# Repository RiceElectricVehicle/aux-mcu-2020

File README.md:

# Central Controller Code

Initial Author: Boyuan Deng

## Overview

This library is built for Rice Electric Vehicle Electric Team's auxilary board (aux board). The main function of the auxilary board include the following:

1. Take in and respond to information from pedal and break
2. Communicate with and respond to motor controller
3. Enable lighting control through switches installed on board
4. Display the car's status on screen

All the functions mentioned above requires the microcontroller on aux board. We've chosen Teensy 3.5 as the microcontroller, and the language for it is Arduino language, which is essentially C++ with Arduino's special libraries. We chose Serial Peripheral Interface (SPI) as the protocol between the aux board and the motor controller board. The following sections will detail the libraries and files contained in the library.

## External Libraries

Besides main.cpp, there are two external libraries under the /lib directory. You can add additional directories to /lib. Refer to the README under /lib to find out how to do that.

### Arduino-PID-Library-master

The Proportioal-Integral-Derivative (PID) control is a control loop mechanism used widely in industry. If you are unfamiliar with this, be sure to do some online research to understand it. The basic idea is to read a sensor, then compute the desired actuator output by calculating proportional, integral, and derivative responses and summing those three components to compute the output.

This library is an external libarary provided by Arduino. It is currently unused as the PID functionality has been taken care of by the motor controller. However, it still comes handy if you ever want PID in aux board. The constructor of the class is as below:
```
PID(double* Input, double* Output, double* Setpoint, double Kp, double Ki,
         double Kd, int POn, int ControllerDirection)
```
The PID input will be stored in first pointer, and the output second pointer, the setpoint third pointer. Three constants Kp, Ki and Kd are also required. You can specify the direction by last variable. A typical initialization of a PID object would look like below:
```
double pid_inA, pid_outA, pid_setA;
PID pidA(&pid_inA, &pid_outA, &pid_setA, 1, 1, 0, REVERSE);
```
Then in the main loop, you call
```
pidA.Compute();
```
And then `pid_outA` will contain desired output.

### OLED

This is a library that I personally write to drive the OLED screen. **Please install U8g2 in PlatformIO/your preferred IDE before it will work!** It is dependent on U8g2 libarary. A typical initialization would look like this:
```
OLED OLED_screen;
```
Internally a U8g2 screen object of the required type will be initialized. Then in your setup() routine, initializa the object by passing in a pointer to a location where the speed/power/whatever you want to show is stored:
```
OLED_screen.init(&speed);
```
After that, you can call it's functions like `display_braking`, `display_speed` etc. Some functions inside it is outdated, and you can add or replace some of them if you want.

## Main Code

Under /src directory are main control algorithms for the car.

### pins.h

Here we define necessary pins for main.cpp to use. In this way, we no longer need to memorize the pins for each functionality after we settled the design. You can find a pinout for Teensy 3.5 here:

https://www.pjrc.com/teensy/card8a_rev2.pdf

### main.cpp

This is the main control algorithm for aux board. I will explain some important variables I declared before I move to the algorithm itself.

##### Data

In SPI communication, we are transmitting 16 bits of information in forms of an integer. Manipulating this integer is a little trouble some, and `Data` is more easy to play with. `create_data()`, `decode_data()`, `encode_data()` and `print_data()` are self-explanatory helper functions to aid transition between struct and int.

##### Message ints

```
volatile unsigned int message_A_out;
volatile unsigned int message_A_in = 0;
volatile unsigned int message_B_out;
volatile unsigned int message_B_in = 0;
```
These are the variables we use to receive and send information over SPI. Rules for their encoding is explained in next section.

##### brk, direction and error

These are global variables keeping track of current state of the car.

##### The IntervalTimer objects

```
IntervalTimer clock_timer;
IntervalTimer SPI_timer;
```
These two IntervalTimer objects utilizes Teensy 3.5's hardware timed interrupts. They send out interrupt signals every certain amount of time, so that the designated function will execute every fixed amount of time. Meanwhile, main loop will pause.

#### The setup() routine

Here a few things need to be set up:

1. Set pinMode for necessary pins
2. Serial monitor, enabling debugging
3. Interrupt for break, as well we the IntervalTimer objects
4. SPI communication
5. OLED screen object

Refer to the code comments for implementation details.

#### The loop() routine

Currently useless. Important routines are wrapped inside IntervalTimer objects so they can be steadily and predicably executed every certain amount of time. However, potentially it can be used to monitor motor controller's state and react to it accordingly.

#### The blink() routine

This function send out signals to toggle headlight every half a second, so that it blinks.

#### The brake_isr() routine

Whenever there is a change in the `BRAKE_SNS` pin, this function will be executed. If it is activated when the current state is breaking, that means the brake is released. Otherwise, it means that the brake is been activated, then the current state is changed and we communicate with motor controller this change.

#### The get_and_send() routine

The core routine of main.cpp. First we read in values indicating position of the pedal. We then send this information along with current state over to motor controller. Note that you need to pull the pins low before you transmit the information, and pull the pins high after you finished.

## SPI specification

The information we send over in SPI is an 16-bit integer.

### 4 Most Significant Bits

4MSBs indicat the current state of the car. 1st bit indicate brake, 2nd bit direction, 3rd bit error, 4th bit currently left empty and for future use. For brake and error, 1 indicate "have" while 0 indicate "do not have" (e.g. 1 in brake indicate braking). For direction, 1 is forward while 0 is backward.

### 12 lower bits

12 lower bits are for set points. This allows for a resolution of 1/4096 for set points. The actual representation of the set points are by no means fixed, and feel free to change if you see fit.

### To conclude:

Brake|Direction|Error|Blank|12 bits of set point

#### Exersise:

What does 1100000000001111 mean?

Answer: Braking, forward, no errors and a setpoint of 31.

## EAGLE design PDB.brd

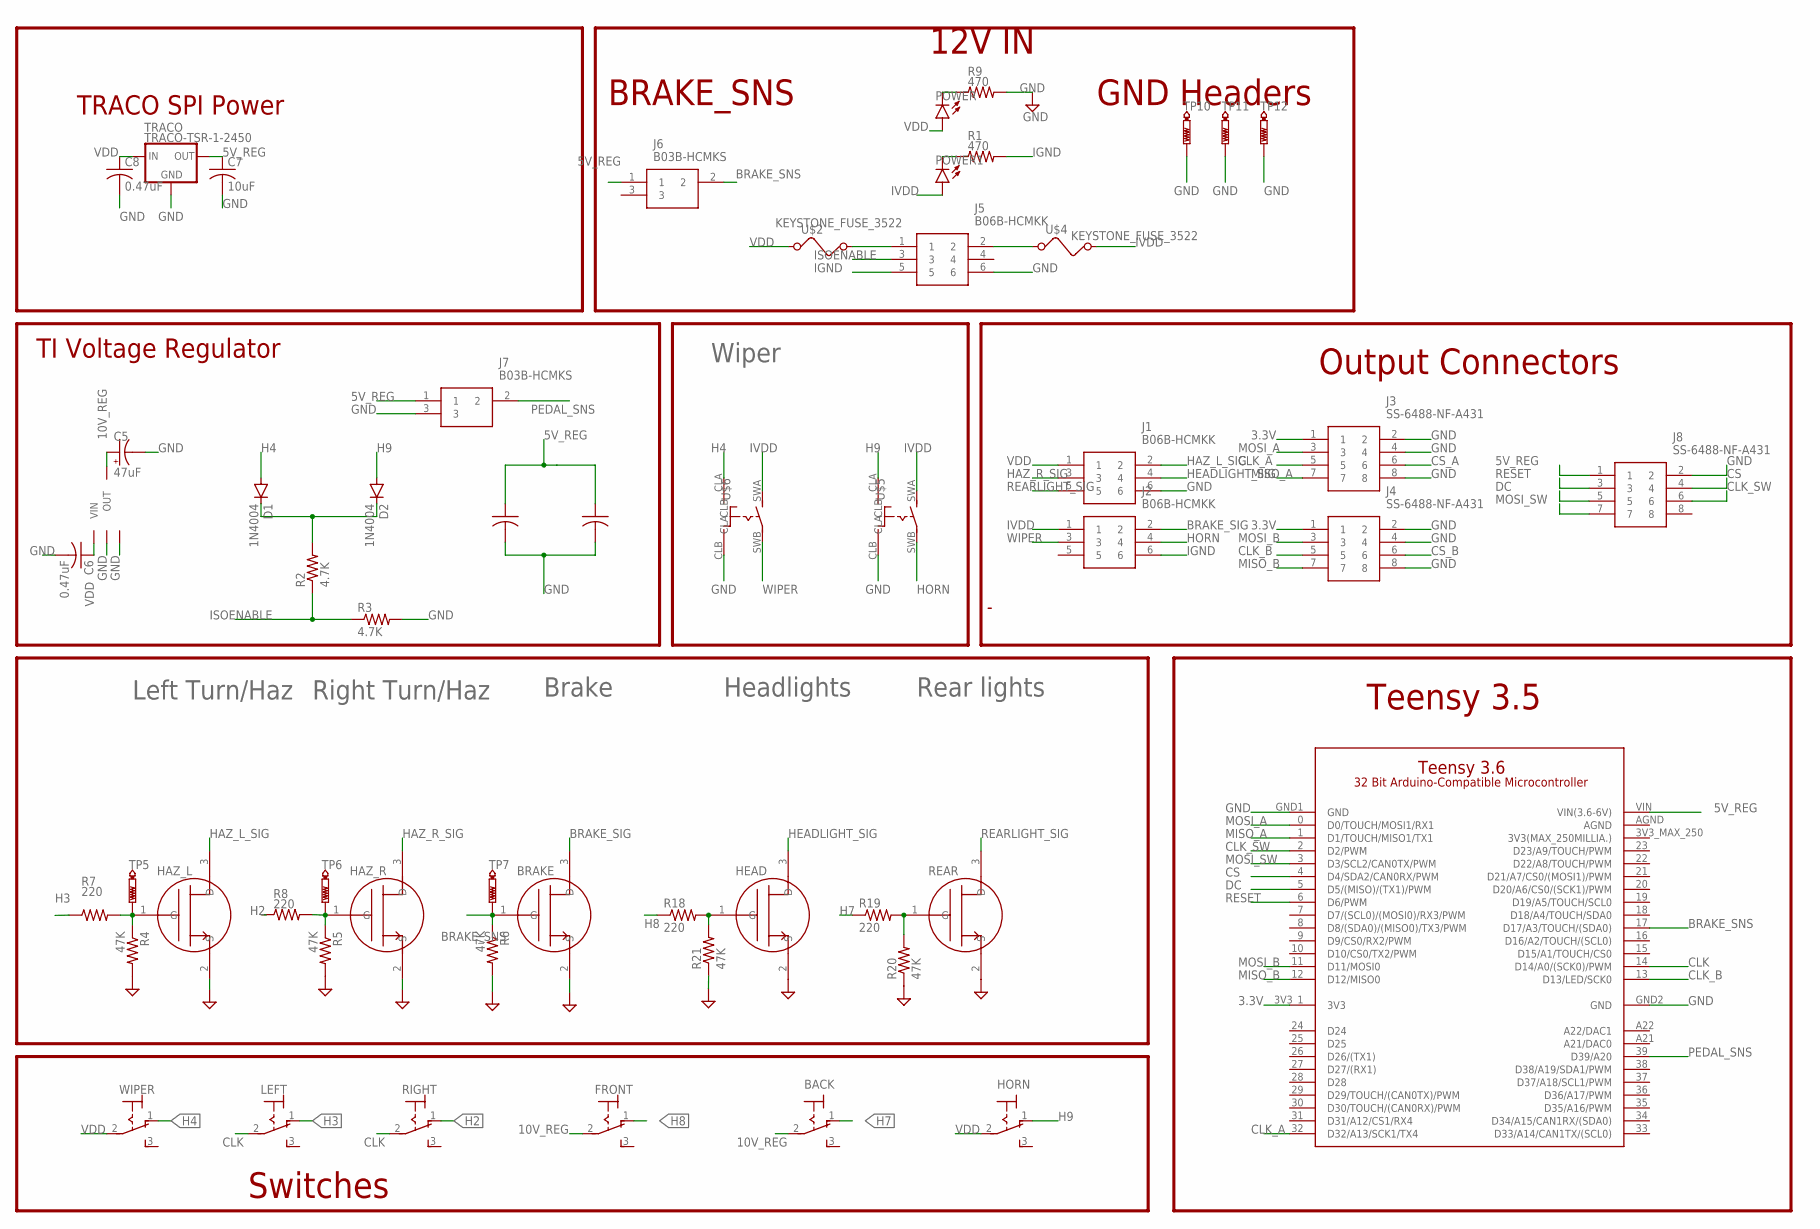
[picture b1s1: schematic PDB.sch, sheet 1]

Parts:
BACK: M9040P
BRAKE: NCV8405ADPAK-3PIN; TO254P1054X240-3
C1: 0.1uF; C0805
C2, C7: 10uF; C0805
C5: 47uF; PANASONIC_C
C6, C8: 0.47uF; C0805
D1, D2: 1N4004; DO41-10
FRONT: M9040P
HAZ_L: NCV8405ADPAK-3PIN; TO254P1054X240-3
HAZ_R: NCV8405ADPAK-3PIN; TO254P1054X240-3
HEAD: NCV8405ADPAK-3PIN; TO254P1054X240-3
HORN: M9040P
J1, J2, J5: B06B-HCMKK; B06BHCMKK
J3, J4, J8: SS-6488-NF-A431; SS6488NFA431
J6, J7: B03B-HCMKS; B03BHCMKS
LEFT: M9040P
LM2940: LM2940LM; SOT230P700X180-4
POWER, POWER1: LEDCHIPLED_0805; CHIPLED_0805
R1, R9: 470; R3225
R2, R3: 4.7K; R0805
R4, R5, R6, R20, R21: 47K; R0805
R7, R8, R18, R19: 220; R0805
REAR: NCV8405ADPAK-3PIN; TO254P1054X240-3
RIGHT: M9040P
TP5, TP6, TP7: PTR1B2,54; B2,54
TP10, TP11, TP12: PTR1PAD1-13Y; P1-13Y
TRACO: TRACO-TSR-1-2450; SIP3
U$2, U$4: KEYSTONE_FUSE_3522
U$3: TEENSY-3.6_ONLY_HOLES
U$5, U$6: TE_CON_OJE-SH-112DM,095\; TE_CON_OJE-SH-112DM,095
WIPER: M9040P

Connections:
3.3V: J3.1, J4.1, U$3.3V3_1 (3V3)
5V_REG: C1.1, C2.1, C7.1, J6.1, J7.1, J8.1, TRACO.3 (OUT), U$3.VIN (VIN(3.6-6V))
10V_REG: BACK.2, C5.+, FRONT.2, LM2940.3 (OUT)
AGND: U$3.AGND
BRAKE_SIG: BRAKE.3 (D), J2.2
BRAKE_SNS: BRAKE.1 (G), J6.2, R6.1, TP7.TP, U$3.17 (D17/A3/TOUCH/(SDA0))
CLK: LEFT.2, RIGHT.2, U$3.14 (D14/A0/(SCK0)/PWM)
CLK_A: J3.5, U$3.32 (D32/A13/SCK1/TX4)
CLK_B: J4.5, U$3.13 (D13/LED/SCK0)
CLK_SW: J8.6, U$3.2 (D2/PWM)
CS: J8.4, U$3.4 (D4/SDA2/CAN0RX/PWM)
CS_A: J3.6
CS_B: J4.6
DC: J8.5, U$3.5 (D5/(MISO)/(TX1)/PWM)
GND: BRAKE.2 (S), C1.2, C2.2, C5.-, C6.2, C7.2, C8.2, HAZ_L.2 (S), HAZ_R.2 (S), HEAD.2 (S), J1.6, J3.2, J3.4, J3.8, J4.2, J4.4, J4.8, J5.6, J7.3, J8.2, LM2940.2 (GND2), LM2940.4 (GND), R3.2, R4.2, R5.2, R6.2, R9.2, R20.1, R21.1, REAR.2 (S), TP10.TP, TP11.TP, TP12.TP, TRACO.2 (GND), U$3.GND1 (GND), U$3.GND2 (GND), U$5.CLB, U$6.CLB
H2: R8.1, RIGHT.1 (O)
H3: LEFT.1 (O), R7.1
H4: D1.A, U$6.CLA, WIPER.1 (O)
H7: BACK.1 (O), R19.1
H8: FRONT.1 (O), R18.1
H9: D2.A, HORN.1 (O), U$5.CLA
HAZ_L_SIG: HAZ_L.3 (D), J1.2
HAZ_R_SIG: HAZ_R.3 (D), J1.3
HEADLIGHT_SIG: HEAD.3 (D), J1.4
HL_GATE: HAZ_L.1 (G), R4.1, R7.2, TP5.TP
HORN: J2.4, U$5.SWB
HR_GATE: HAZ_R.1 (G), R5.1, R8.2, TP6.TP
IGND: J2.6, J5.5, R1.2
ISOENABLE: J5.3, R2.1, R3.1
IVDD: J2.1, POWER1.A, U$4.B1 (2), U$4.B2 (2), U$5.SWA, U$6.SWA
MISO_A: J3.7, U$3.1 (D1/TOUCH/MISO1/TX1)
MISO_B: J4.7, U$3.12 (D12/MISO0)
MOSI_A: J3.3, U$3.0 (D0/TOUCH/MOSI1/RX1)
MOSI_B: J4.3, U$3.11 (D11/MOSI0)
MOSI_SW: J8.7, U$3.3 (D3/SCL2/CAN0TX/PWM)
unnamed: POWER.C, R9.1
unnamed: D1.C, D2.C, R2.2
unnamed: J5.1, U$2.B1 (2), U$2.B2 (2)
unnamed: J5.2, U$4.A1 (1), U$4.A2 (1)
unnamed: POWER1.C, R1.1
unnamed: HEAD.1 (G), R18.2, R21.2
unnamed: R19.2, R20.2, REAR.1 (G)
PEDAL_SNS: J7.2, U$3.39 (D39/A20)
REARLIGHT_SIG: J1.5, REAR.3 (D)
RESET: J8.3, U$3.6 (D6/PWM)
VDD: C6.1, C8.1, HORN.2, J1.1, LM2940.1 (VIN), POWER.A, TRACO.1 (IN), U$2.A1 (1), U$2.A2 (1), WIPER.2
WIPER: J2.3, U$6.SWB

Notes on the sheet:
12V IN
BRAKE_SNS
Switches
Wiper
Left Turn/Haz
Right Turn/Haz
Brake
Headlights
Rear lights
GND Headers
Output Connectors
TRACO SPI Power
TI Voltage Regulator
Teensy 3.5

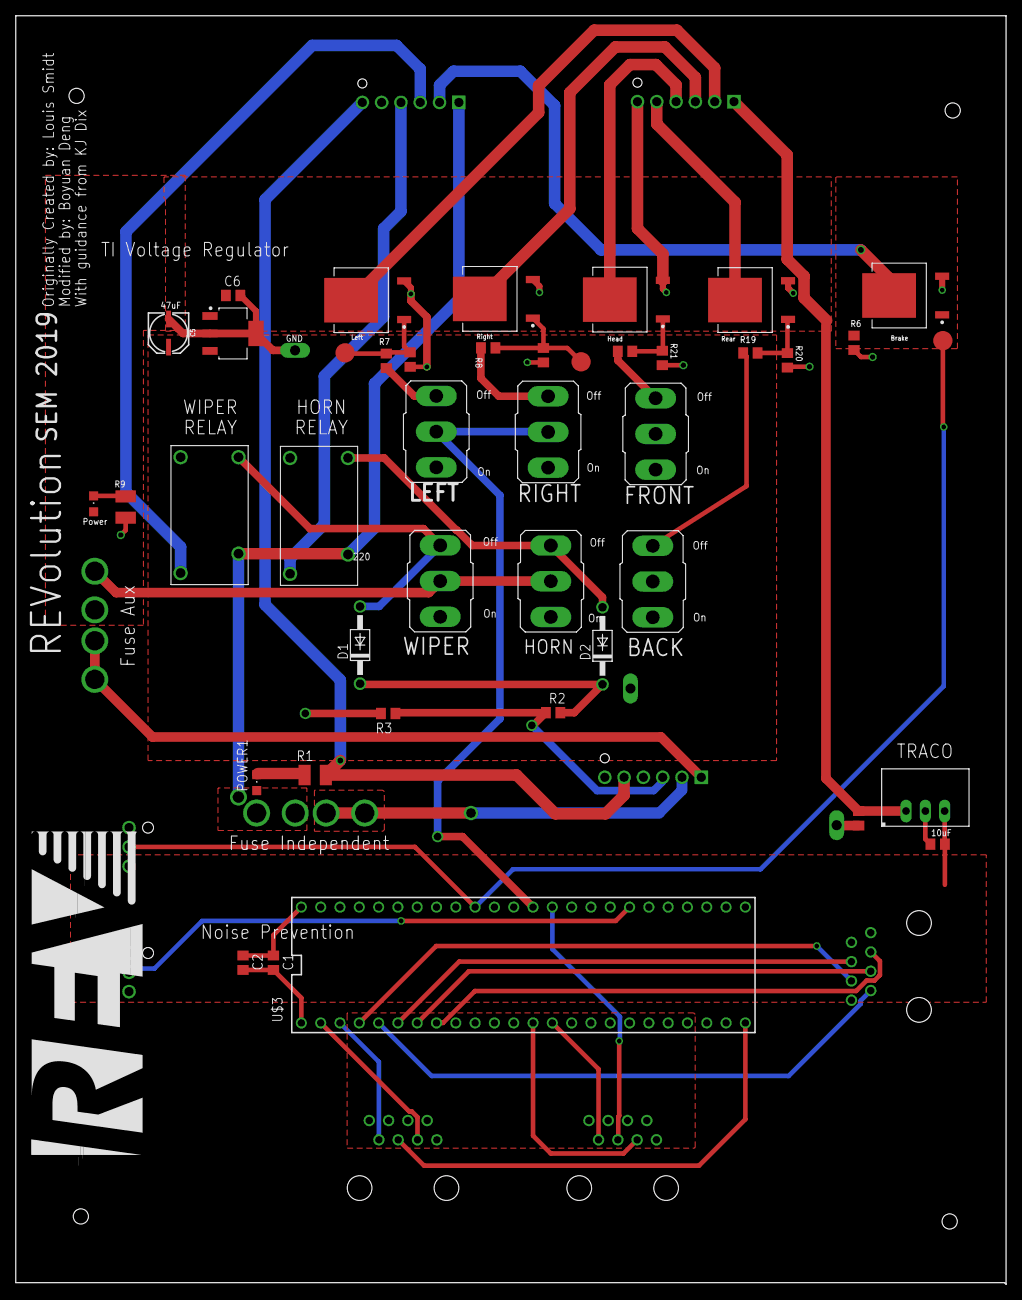
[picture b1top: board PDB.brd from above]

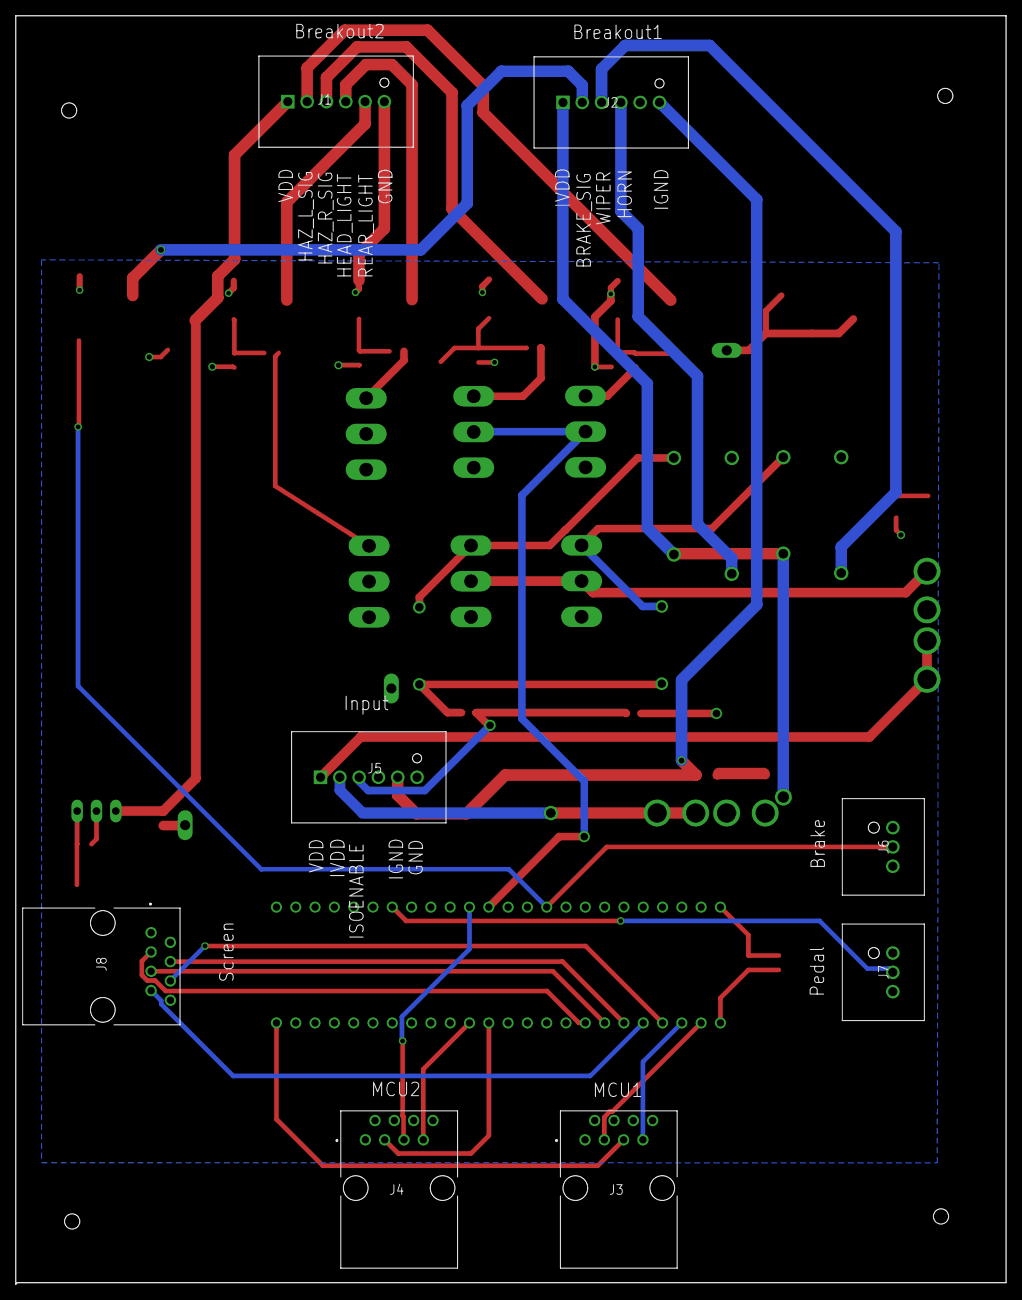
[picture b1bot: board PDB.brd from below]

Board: 2 copper layers, 130.3 x 166.9 mm, 55 parts (8 on the bottom side), 44 nets.

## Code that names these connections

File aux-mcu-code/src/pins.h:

#ifndef PINS_H
#define PINS_H

// Motor controller A
#define MOSI_A 0
#define MISO_A 1
#define SS_A 31
#define CLK_A 32

// Motor controller B
#define MOSI_B 11
#define MISO_B 12
#define SS_B 15
#define CLK_B 13

// Screen SPI
#define MOSI_SW 3
#define CS 4
#define DC 5
#define RESET 6
#define CLK_SW 2

// Clock signal
#define CLK 14

// Pedal
#define PEDAL_SNS 39

// Brake
#define BRAKE_SNS 17

#endif  // PINS_H

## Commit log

2019-10-19 Aux board from last year
2019-10-26 Deleted SPI, ADD2
2019-10-26 Changed GND to VDD for connector
2019-10-28 Disconnected 555-timer from the jumper
2019-10-28 Deleted Anderson connector for left and right light
2019-10-28 Last time forget to save. This is the real version of last commit.
2019-10-29 Deleted most Anderson connectors. Brake sensor waiting to be modified
2019-10-30 adds project library to build parts in
2019-10-30 adds new connectors and relays, and removes old connectors and wiper fet
2019-11-01 added master library to repository
2019-11-01 Schemetic first draft done
2019-11-01 Schematic first version
2019-11-01 Board layout proposal
2019-11-02 Board first version
2019-11-02 Decorative modification
2019-11-02 VIPER misspelling corrected
2019-11-05 Widen the traces of independent 12V and indipendent ground
2019-11-07 Added voltage divider so that Teensy 3.5 sees Wiper and Horn are turned on
2019-11-12 With diode, pass signal direcely to ISOENABLE
2019-11-19 Flipped all connectors to the back side, added capacitors connecting Teensy's 5V_REG to GND
2019-11-19 Silkscreen finished.
2019-11-19 slightly moved traces that were close
2019-11-19 Adjusted schematic and routing to pass twisted pairs to each signal
2019-11-23 switched order of output bus
2019-11-24 Edited skilscreen to fit new connector arrangement, reversed ethernet cable to screen to correct direction.
2020-01-25 Code folder added.
2020-01-25 Finished definition for pins.h
2020-01-25 Changed OLED folder modified for software SPI.
2020-01-25 Implemented data transfer structure and its decode and encode methods.
2020-01-30 Added blinking to headlights, added in break sense.
2020-02-04 Set up the PID.
2020-02-27 adds cs signal but does not route it
2020-02-29 Changed the testing bits.
2020-03-05 Debugged SPI.
2020-03-07 Changed SPI from loop to interrupts.
2020-03-07 Everythings works now.
2020-04-21 Written support documents.
2020-04-21 Moved this document.
2020-04-21 Added compile instructions.

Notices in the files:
parts and their libraries:
SparkFun-Capacitors: Licensing: Creative Commons ShareAlike 4.0 International - https://creativecommons.org/licenses/by-sa/4.0
